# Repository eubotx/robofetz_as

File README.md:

# ROBOFETZ_AS

ROBOFETZ_AS is a hands-on project for learning combat robot autonomy with ROS 2
Jazzy. It combines arena perception, localization, strategy, navigation, and
robot control. Elf is the default strategy in Gazebo and on the physical robot.

## Robot hardware

| Elfbar prototype | CAD model |
| --- | --- |
|  |  |

## Choose how to run it

| Approach | Choose it when | How it runs |
| --- | --- | --- |
| **VS Code Dev Container** | You want to edit, build, and test ROS packages. | VS Code opens your checkout inside a container. Gazebo and RViz appear in a browser desktop, with optional Xbox controller passthrough for the simulated opponent. |
| **Standalone Docker Compose** | You want to run the simulator from a terminal without an editor. | Compose builds an image from the current checkout and serves the simulation desktop in your browser. Rebuild the image after changing source. |
| **Native Ubuntu 24.04** | You want to connect the real robot or run ROS directly on your workstation. | ROS 2 Jazzy and Gazebo run on the host. Use Gazebo for simulation or connect the arena camera, radio bridge, and gamepad for hardware bringup. |

Both container workflows supply ROS and Gazebo and are configured for
simulation. On Windows, use either workflow from Ubuntu 24.04 under WSL 2.
The keyboard works in both workflows. The optional Xbox profile needs a
controller input device visible to the Linux Docker host.

[Installation and first run](docs/installation.md) ·
[Dev Container workflow](docker/DEVCONTAINER.md) ·
[Xbox controller passthrough](docker/DEVCONTAINER.md#xbox-controller-passthrough) ·
[Docker Compose workflow](docker/README.md)

## Project documentation

- [System architecture](docs/architecture.md) traces the data flow from the arena camera to the robot.
- [Autonomy guide](docs/autonomy.md) explains Elf and the available strategy variants.
- [Package guides](docs/packages/README.md) cover node interfaces and launch options.
- [Firmware guide](docs/firmware.md) covers the ESP32 and radio link.
- [Contributor guide](AGENTS.md) covers workspace conventions and validation.

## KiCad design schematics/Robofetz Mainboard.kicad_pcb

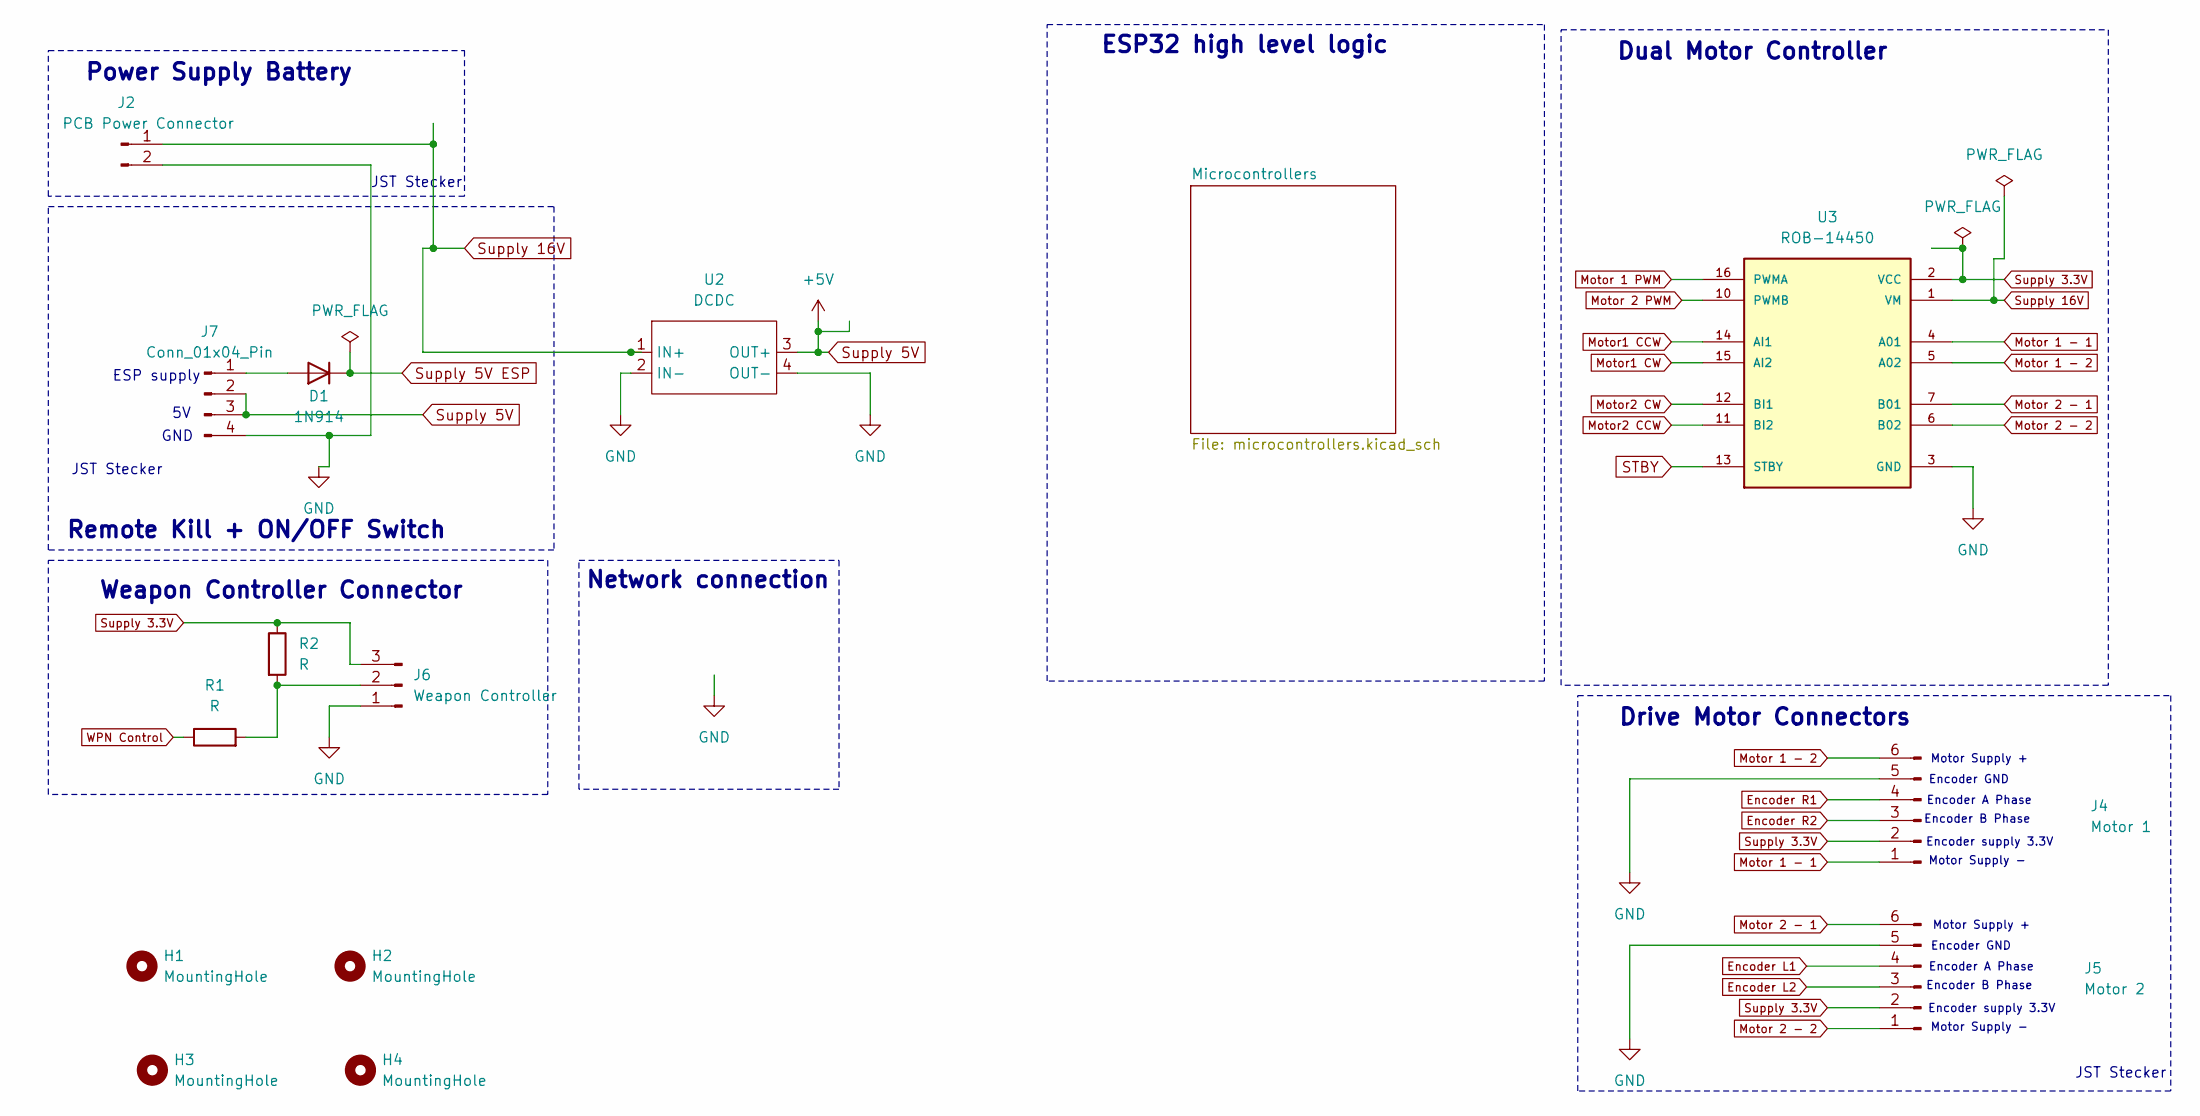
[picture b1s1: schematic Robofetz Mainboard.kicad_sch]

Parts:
D1: 1N914; D_DO-35_SOD27_P7.62mm_Horizontal
H1, H2, H3, H4: MountingHole; MountingHole_2.1mm
J2: PCB Power Connector; JST_EH_B2B-EH-A_1x02_P2.50mm_Vertical
J4: Motor 1; JST_EH_B6B-EH-A_1x06_P2.50mm_Vertical
J5: Motor 2; JST_EH_B6B-EH-A_1x06_P2.50mm_Vertical
J6: Weapon Controller; JST_EH_B3B-EH-A_1x03_P2.50mm_Vertical
J7: Conn_01x04_Pin; JST_EH_B4B-EH-A_1x04_P2.50mm_Vertical
R1, R2: R; R_Axial_DIN0204_L3.6mm_D1.6mm_P1.90mm_Vertical
U2: DCDC; buck_converter_robofetz
U3: ROB-14450; ROB14450; PARTREV 11-13-17

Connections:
Encoder L1: J5.4; also elsewhere on the board
Encoder L2: J5.3; also elsewhere on the board
Encoder R1: J4.4; also elsewhere on the board
Encoder R2: J4.3; also elsewhere on the board
GND: J2.2, J4.5, J5.5, J6.1, J7.4, U2.2 (IN-), U2.4 (OUT-), U3.3 (GND), U3.8 (GND), U3.9 (GND); also elsewhere on the board
Motor1 CCW: U3.14 (AI1); also elsewhere on the board
Motor1 CW: U3.15 (AI2); also elsewhere on the board
Motor2 CCW: U3.11 (BI2); also elsewhere on the board
Motor2 CW: U3.12 (BI1); also elsewhere on the board
Motor 1 - 1: J4.1, U3.4 (A01)
Motor 1 - 2: J4.6, U3.5 (A02)
Motor 1 PWM: U3.16 (PWMA); also elsewhere on the board
Motor 2 - 1: J5.6, U3.7 (B01)
Motor 2 - 2: J5.1, U3.6 (B02)
Motor 2 PWM: U3.10 (PWMB); also elsewhere on the board
unnamed: D1.2 (A), J7.1
unnamed: J6.2, R1.2, R2.2
STBY: U3.13 (STBY); also elsewhere on the board
Supply 3.3V: J4.2, J5.2, J6.3, R2.1, U3.2 (VCC); also elsewhere on the board
Supply 5V: J7.2, J7.3, U2.3 (OUT+)
Supply 5V ESP: D1.1 (K); also elsewhere on the board
Supply 16V: J2.1, U2.1 (IN+), U3.1 (VM)
WPN Control: R1.1; also elsewhere on the board

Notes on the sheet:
Encoder B Phase
Encoder GND
Remote Kill + ON/OFF Switch
Motor Supply -
JST Stecker
ESP supply
Weapon Controller Connector
ESP32 high level logic
Motor Supply +
Encoder A Phase
Drive Motor Connectors
Encoder supply 3.3V
Network connection
Dual Motor Controller
GND
Power Supply Battery

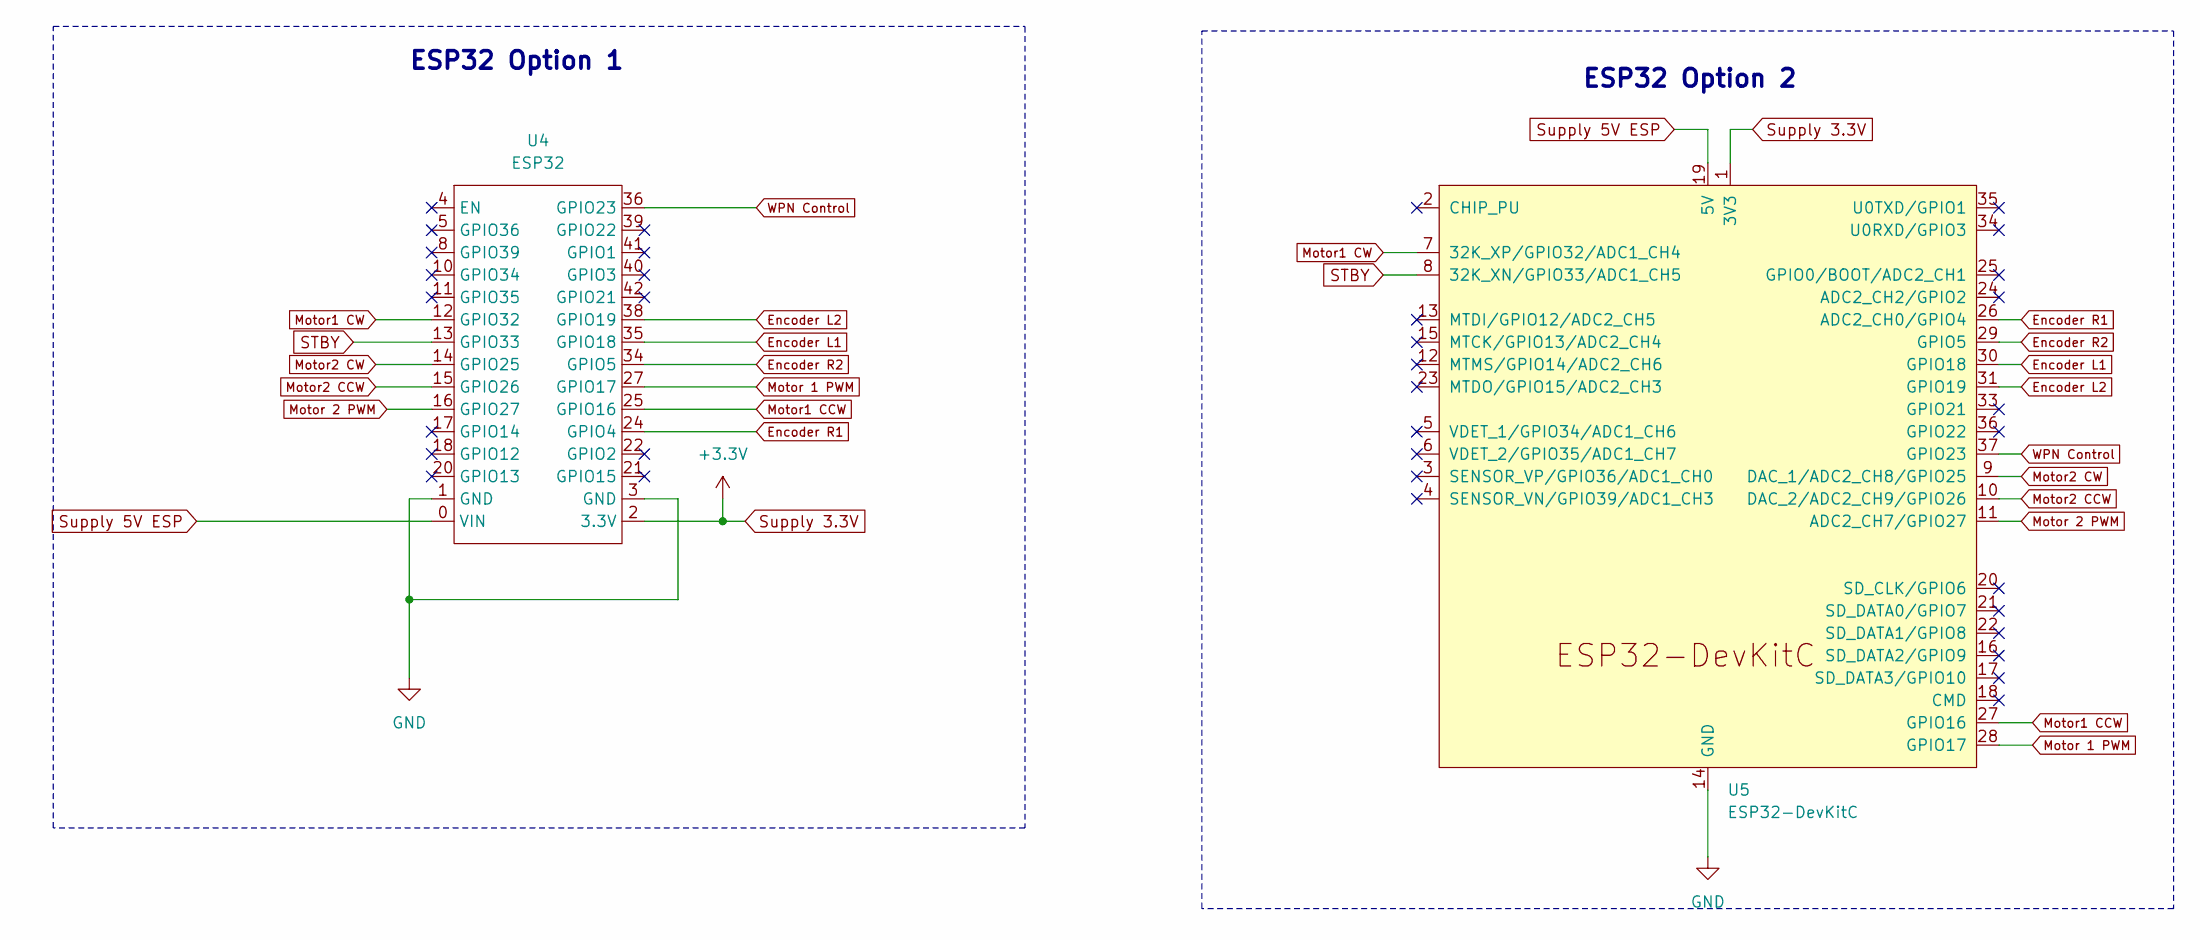
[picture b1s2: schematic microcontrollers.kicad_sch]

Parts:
U4: ESP32; ESP32_devboard
U5: ESP32-DevKitC

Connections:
Encoder L1: U4.35 (GPIO18), U5.30 (GPIO18); also elsewhere on the board
Encoder L2: U4.38 (GPIO19), U5.31 (GPIO19); also elsewhere on the board
Encoder R1: U4.24 (GPIO4), U5.26 (ADC2_CH0/GPIO4); also elsewhere on the board
Encoder R2: U4.34 (GPIO5), U5.29 (GPIO5); also elsewhere on the board
GND: U4.1 (GND), U4.3 (GND), U5.14 (GND), U5.32 (GND), U5.38 (GND); also elsewhere on the board
Motor1 CCW: U4.25 (GPIO16), U5.27 (GPIO16); also elsewhere on the board
Motor1 CW: U4.12 (GPIO32), U5.7 (32K_XP/GPIO32/ADC1_CH4); also elsewhere on the board
Motor2 CCW: U4.15 (GPIO26), U5.10 (DAC_2/ADC2_CH9/GPIO26); also elsewhere on the board
Motor2 CW: U4.14 (GPIO25), U5.9 (DAC_1/ADC2_CH8/GPIO25); also elsewhere on the board
Motor 1 PWM: U4.27 (GPIO17), U5.28 (GPIO17); also elsewhere on the board
Motor 2 PWM: U4.16 (GPIO27), U5.11 (ADC2_CH7/GPIO27); also elsewhere on the board
STBY: U4.13 (GPIO33), U5.8 (32K_XN/GPIO33/ADC1_CH5); also elsewhere on the board
Supply 3.3V: U4.2 (3.3V), U5.1 (3V3); also elsewhere on the board
Supply 5V ESP: U4.0 (VIN), U5.19 (5V); also elsewhere on the board
WPN Control: U4.36 (GPIO23), U5.37 (GPIO23); also elsewhere on the board

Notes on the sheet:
ESP32 Option 2
ESP32 Option 1

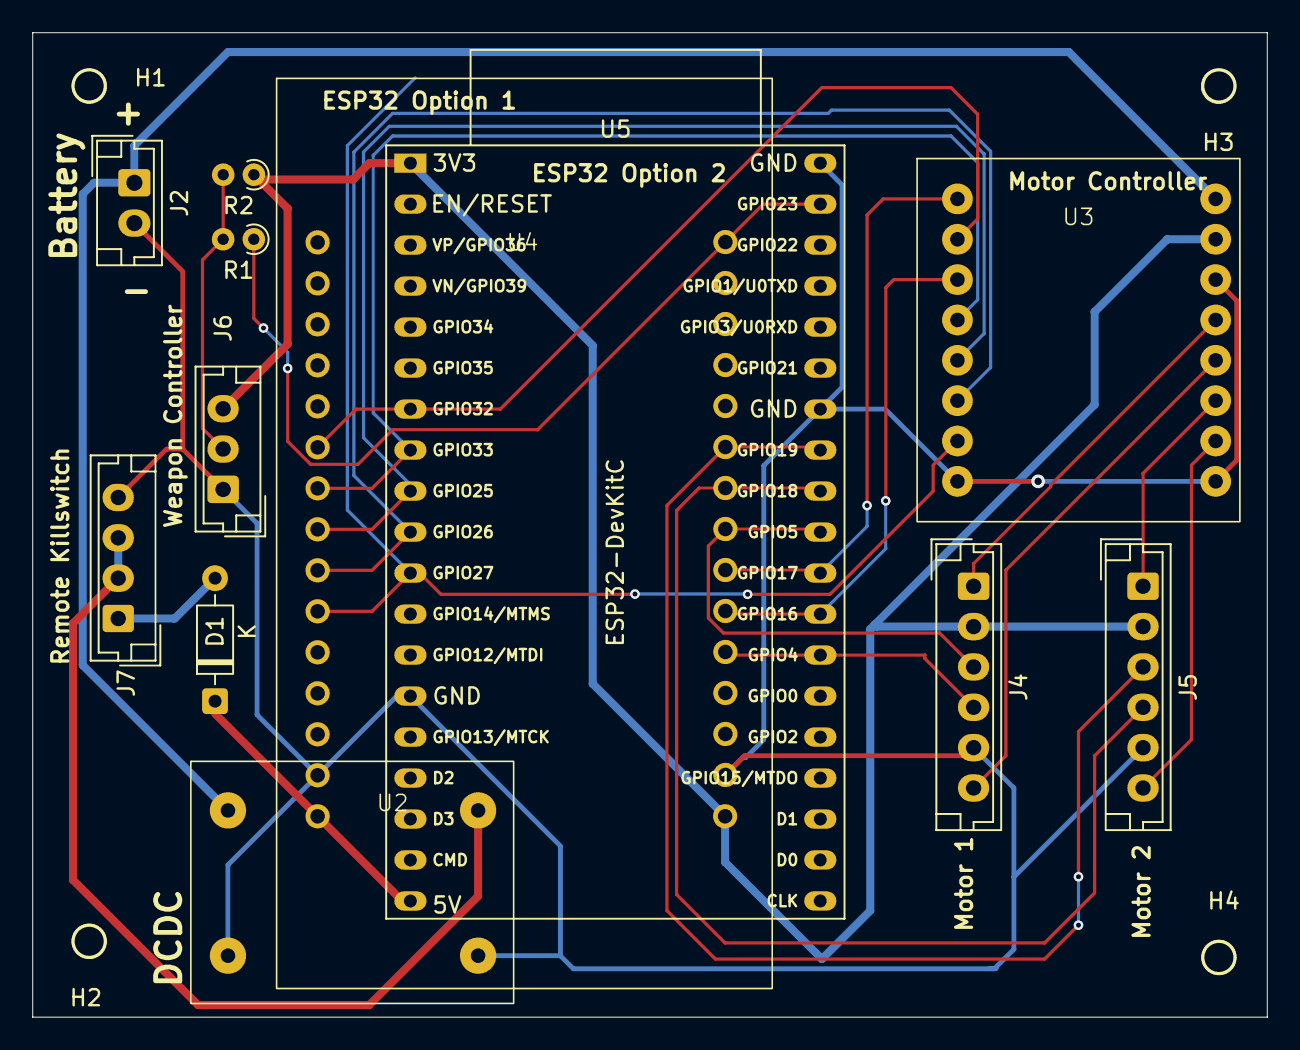
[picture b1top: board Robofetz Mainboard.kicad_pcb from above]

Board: 2 copper layers, 76.5 x 61.0 mm, 16 parts (0 on the bottom side), 23 nets.

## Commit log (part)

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2025-09-23 made basic usb cam node working with cam configs
2025-11-07 save progress before user specific params
2025-11-07 video device settings works really nicely now for multiple users with environment variables
2025-11-07 camera info manager working variant 1
2025-11-07 variant 2 working via config file
2025-11-07 variant2 working really nicely with env also now. Next up: -fill in correct lens distortions -play around with gui for parameters -shift to ros_camera
2025-11-08 minor updates to how video device is handled. next image proc
2025-11-08 image proc has no good fisheye model. implemented fisheye model myself. for now in python.
    Todo:
    -change rectification to cpp
    -fix right hand side of rectification matrix
    -better integrate rectification tool
    Other Todo:
    -test ros_camera
2025-11-09 started to make camera_ros working, rqt reconfigure works good
2025-11-09 vibe coded robot detection & arena calibration with old code as its own ros nodes, looks good
2025-11-09 massive cleanup of old detection code. enemy still to do
2025-11-13 not running checkpoint version before major simplifications of transforms
2025-11-13 nodes interacting perfectly fine
    todos:
    -april tag size to be calibrated
    -generally april tag data should be ros configurable parameters
2025-11-15 now robot_base. static robot_tag tf should come from something else. also arena detection detached from other nodes, but still a callable service with initial calibration. untested code
2025-11-17 gazebo now has a arena_camera
2025-11-17 now with fisheye cam
2025-11-17 big cleanup
2025-11-26 renamed enemy->opponent and model->models
2025-11-26 renamed simple_diff_drive_sim -> robofetz_gazebo
2025-11-26 minor fix of last commit
2025-11-30 bump submodule fisheye-camere-undistortion
2025-12-02 reorganized gazebo models
2025-12-02 now worlds with pinhole and wideangle and gazebo models environment path done nicely
2025-12-02 minor renaming but leads to changes in other nodes
2025-12-05 added arena apriltag
2025-12-05 now wideangle and pinhole usable with auto adjusting camera info publisher
2025-12-05 rectification now handles both pinhole and wideangle
2025-12-10 made world the super parent tf. introduced arena.yaml
2025-12-10 not working commit with camera optical
2025-12-10 still not working
2025-12-10 still not working but simple
2025-12-10 not working but even simpler
2025-12-10 dirty fixed but working
2025-12-10 renamed detection to arena_perception
2025-12-10 cleanup fisheye submodule
2025-12-10 readded submodule
2025-12-10 final touches before merge
2025-12-13 Added first attemof map_node and keyboard node
2025-12-14 fixed prefix error
2025-12-21 small remarks
2025-12-21 fixed navigator issue with simple attack.
2025-12-22 Made TF tree compliant with nav2
2025-12-25 Updated map creation tool and gimp support
2025-12-25 cleanup
2025-12-25 cleanup + fixed map issues
2025-12-25 nav2 first attempt: MAP SERVER working!
2025-12-26 updated keyboard node + updated nav2 stack
2025-12-27 increased map size to circumvent the out of bounds error
2025-12-27 update: NAV2 implementation working!
2025-12-29 Adpated parameters to have sliples simulation for further testing
2025-12-29 Adjusted to meet real dimensions
2025-12-30 oponent tracker node added
2026-01-02 Node Update, Overshoot-fix
2026-01-02 Added delay to nav2 launch to make system more robust. Adapted nav2 parameters to collide with enemy
2026-01-03 - Added schematics - added footprints
2026-01-03 Apriltags working on robot
2026-01-03 added correct apriltags
2026-01-03 at least it runs but coordinates are messed up
2026-01-03 Updated KiCAD
2026-01-03 Republish cmd_vel_smoothed to cmd_vel
2026-01-03 Added libraries
2026-01-04 Updated libararies, passed ERC
2026-01-04 Finished PCB Version 1
2026-01-04 added rviz config
2026-01-04 feat: Add arena ball model, teleop opponent launch, and enhance opponent tracker with parameter tuning, diagnostics, and robot friction adjustments.
2026-01-04 save
2026-01-04 updated schematics + pcb layout
2026-01-04 refactor: Remove velocity vector drawing from opponent tracker visualization.
2026-01-05 added camera calibration board
2026-01-05 updated schematics + layout
2026-01-05 robot detection now working roughly
2026-01-05 updated layout
2026-01-05 fixed coordinate system fixes with apriltag
2026-01-05 robot debug image not working. otherwise working but smoothing needed
2026-01-05 updated lazout
2026-01-05 good but debug image not working
2026-01-05 minimal but laggy
2026-01-05 works but still laggy
2026-01-05 works good enough for now. next architecture rework with one april detection node in c
2026-01-06 now working not laggy - only filtering todo
2026-01-06 first filtering done
2026-01-06 rudimentary filtering done
2026-01-06 init
2026-01-06 cleaned up camera configs and made camera work with 60fps in mjpeg
2026-01-07 fixed costmap error
2026-01-07 map node that publishes a map according to the opponent/pose_sim
2026-01-07 topic fix
2026-01-08 some good progress on urdf
2026-01-08 robot adjusted to testbot
2026-01-09 fixed map error
2026-01-10 big reorga of robot description location
2026-01-10 more cleanup and started to implement proper map->odom correction
2026-01-11 fixed map missalignement issue
2026-01-11 tf chaining working
2026-01-11 it worksss
2026-01-11 apriltag rework of old node started
2026-01-11 apriltag rework started
2026-01-11 very nice apriltag detection node
2026-01-12 started work on arena calibration to make it more versatile as camera in world finder
2026-01-12 Checkpoint
2026-01-12 nav2 tuned
2026-01-12 updated map
2026-01-12 works good
2026-01-12 nice calibration checkpoint
2026-01-12 MPPI controller alternative + cleanup in create_amp
2026-01-12 works super nice now just file storing to do
2026-01-13 working nicely just file saving not
2026-01-13 All working except calibration filtering
2026-01-15 robot detection woring
2026-01-15 variable tag combinations
2026-01-15 also publishs detection state
2026-01-15 full robot detection setup working. ready to go for testing
2026-01-15 dirty push robofetz evening
2026-01-20 cleaned up odom drift correction, parameters to do
2026-01-20 cleanup of some configs
2026-01-22 added parameters for odom drift correction node
2026-01-22 robot detection working with parameters
2026-01-23 robot detection deleted pose, investigated disappearing tags
2026-01-24 find camera in world supports parameters and timeout bug fixed
2026-01-24 timeout bugs fixed across all nodes for now
2026-02-04 added correct timeout for find camera service
2026-02-04 added median filtering to marker detection in find camera
2026-02-04 deleted log thinks which were not needed
2026-02-07 started bringup launch cleanup and made esp code work with new pcb
2026-02-08 configs cleaned up
2026-02-08 bringup progress
2026-02-08 robot.launch.py now supports sim and fake localization
2026-02-08 cleanup bringup
2026-02-08 more cleanup of bringup
2026-02-08 added submodules in correct loation
2026-02-08 nav2.launch.py working
2026-02-10 fixed simulation time usage
2026-02-10 enabled opponent fake detection
2026-02-10 cleanup of arg prefix
2026-02-11 working joint states on real robot
2026-02-11 localization config launch bug fixed, rviz config reworked
2026-02-11 started to rework docu
2026-02-12 collected all notes
2026-02-13 cleanup of notes
2026-02-17 working mvp
2026-02-19 proper image rectification step1
2026-02-19 added_new_detectors
2026-02-19 moved camera info publiser into gazebo for pinhole cam
2026-02-19 improved readme
2026-02-19 readme update
2026-02-19 cleaned up camera setup
2026-02-21 robot detection init now more robust
2026-02-21 started nw apriltag node
2026-02-22 tag correction
2026-02-22 firstImplementationOpponentDetection
2026-02-22 little fix
2026-02-22 mog2&color for single detection work
2026-02-23 Added detection specific IDs
2026-02-23 Added Kalman Filter (not tested)
2026-02-26 fixed configs and readme
2026-02-26 quick fix image topics
2026-02-26 readyforSCAMBranch
2026-02-26 fucke em polygons
2026-02-26 lets go robot fast! brum brum
2026-02-27 fps bump
2026-02-27 typo fix
2026-02-27 fixed sim parameter bug of arena tag
2026-02-28 fixed ros2 topics, began strategizer
2026-02-28 Fixed map issues
2026-03-01 first try combat strategizer.
2026-03-01 Crappy but somehow working nav2 strategizer
2026-03-01 mmerge fix
2026-03-01 Added emtpy map.
2026-03-01 Second approach, static defense positions!
2026-03-06 cleanup + fix nav2 strategizer
2026-03-06 fixes
2026-03-06 vibe coded remapper
2026-03-06 tf to pose remapper
2026-03-12 kalman_filter_works->vel- threshold still needed
2026-03-14 opponent detection pipeline complete
2026-03-14 Added new ESP32 Model
2026-03-14 testing results fachschaft
2026-03-15 Launch files cleanup
2026-03-18 simple navigator sofisticated.
2026-03-19 Navigator update, working but configuration issues,
2026-03-21 camera fix
2026-03-22 color selection now init true
2026-03-22 Camera setup
2026-03-22 nav2 fix
2026-03-22 updated, slow but working
2026-03-22 added tf to pose
2026-03-24 merged working opponent detection
2026-03-25 OppDet works in Sim now
2026-03-25 added roi masking
2026-03-25 detection working
2026-03-25 first efforts
2026-03-25 initial transmitter on PC side
2026-03-25 bot updated
2026-03-25 weapon added
2026-03-25 perception and sim updated to new tags
2026-03-25 Tramitter on string base (to make it easier)
2026-03-25 Added Receiver dummy for robot
2026-03-25 Proper File management
2026-03-25 integration fixes opponent detection
2026-03-25 finished opponent detection integration
2026-03-25 Adapted diffdrive bot with funk. Tested communication, response was okay
2026-03-26 neu Funk commit
2026-03-26 roi mask fixed
2026-03-26 updated tranceiver
2026-03-26 interface adaption
2026-03-26 projection matrix used insted of k
2026-03-27 perceptio simpler
2026-03-27 new cam matrix
2026-03-27 cmd_vel_muxer first part done
2026-03-27 flipping works now
2026-03-27 noice
2026-03-27 whatever
2026-03-27 wallcondition update
2026-03-27 works
2026-03-27 continous tracking
2026-03-27 command
2026-03-27 driving both sides works
2026-03-27 integrated
2026-03-27 added PI and P controll
2026-03-27 tuning
2026-03-27 new arena_camera_info_ardu_gruen_1200p
2026-03-27 removed recovery turn
2026-03-27 fixed topic
2026-03-30 cropping works
2026-04-04 First steps to yolo detection
2026-04-04 adjusted naming
2026-04-04 UPDATE: Added Dockerfile
2026-04-04 Updated docker + docker dataset create
2026-04-05 updated Dockerfile, including all packages
2026-04-05 Added notes
2026-04-06 Ignoring datasets
2026-04-07 updated train_yolo
2026-05-30 teleop in bringup launch file and weapon slider gui working
2026-05-30 opponent detection fusion fixed with correct pose output
2026-05-31 bringup complete
2026-06-02 fake arena perception fixed with opponent
